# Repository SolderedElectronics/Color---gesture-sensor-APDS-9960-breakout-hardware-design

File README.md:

# Color and gesture sensor APDS-9960 breakout Hardware Design

## About the Product

|  |
| :----------------------------------------------------------: |
| [Buy Color and gesture sensor APDS-9960 breakout](https://www.solde.red/333002) |

The APDS-9960 is a small sensor that measures four things at once. It recognizes the movements you make in front of it (up, down, left, right) and it can identify the proximity of the object, so you have two more movements: to the sensor and from the sensor. In addition, it has an ambient light sensor and a color sensor which gives red, green, and blue (RGB) colors as output. This sensor with many features was even built into the Samsung Galaxy S5 smartphone.

All gestures are detected at a distance of 10 to 20 cm and it has built-in UV and IR filters to make sure it won’t be confused by other sources of light. Connected using well-known I2C communication.

---

## Repository Contents

This repository contains all design files for Color and gesture sensor APDS-9960 breakout, organized as follows:

- **`CAD` folder**: Contains KiCAD design files, including:
  - Schematics
  - PCB layout
  - Panel PCB layout
  - Source 3D files in Fusion360, if any
  - All files are sorted by version with a detailed change log.
- **`OUTPUTS` folder**: Includes all production-ready files, such as:
  - Bill of Materials (BOM) and interactive BOM (iBOM)
  - PDF versions of schematics
  - 3D `.step` file of the board
  - 3D-printable models
  - Gerber files for PCB manufacturing
  - Image of the pinout of the board
  - Product image
  - Compliance, legal and generic sales documents

Refer to the `Change Log` in the CAD folder for details about updates between versions.

---

## Learn More About the Product

Beyond the repository, explore the following resources:

### Soldered Verify

The **Soldered Verify** system ensures every board you purchase from Soldered is fully functional. It also provides access to exclusive test data for your product. To get started, find the unique Soldered Verify ID on your product's packaging and enter the ID on the [Soldered Verify page](https://soldered.com/verify/) to access test results and additional product details.

### Soldered Community

Soldered Community is your go-to place for technical support. Our engineers track and answer all questions posted there, and it’s a great space for the maker community. Get answers to your questions and solutions for your challenges at [Soldered Community](https://soldered.com/community).

### solde.red

solde.red is an ultimate URL shortener and information hub. Access it by typing solde.red/ followed by your product SKU, e.g., [solde.red/333000](https://solde.red/333000), to find getting-started guides, datasheets, open-source hardware and software files, certifications, images, pinouts, and more. Read more about the shortener [here](https://solde.red/info/).

---

## Contributing

Contributions are welcome! Here’s how you can get involved:

- Submit pull requests to enhance the design or fix issues.
- Report bugs or problems by opening an issue.

We encourage community collaboration to make this product even better.

---

## About Soldered

[Soldered for Makers](https://soldered.com) specializes in designing and manufacturing electronic products tailored for enthusiasts, ranging from hobbyists to professionals. Our portfolio includes electronic boards, sensors, and actuators that are widely utilized in fields such as microelectronics, mechatronics, robotics, programming, and IoT. Every product we offer is designed in-house and built upon open-source hardware and software platforms. Proudly certified and manufactured within the European Union, our catalog likely includes the product you need for your project.

We complement these products with comprehensive tutorials and manuals, product descriptions, schematics, programming codes, and project examples. Our round-the-clock [customer and technical support](https://soldered.com/community) is available for all our products, irrespective of the sales channel. Soldered’s success and services reflect our maker community’s unwavering [trust](https://www.trustpilot.com/review/soldered.com), for which we are deeply grateful. Join our community and create using Soldered products.

---

## License

All Soldered open-source hardware (OSH) is under The TAPR Open Hardware License. Read more in the LICENSE file located in this repository.

**Disclaimer:**

No warranty - all designs in this repository are distributed in the hope that they will be useful, but without any warranty. They are provided "AS IS", therefore without warranty of any kind, either expressed or implied. The entire quality and performance of what you do with the contents of this repository are your responsibility. In no event Soldered Electronics will be liable for your damages, or losses, including any general, special, incidental, or consequential damage arising out of the use or inability to use the contents of this repository. 

---

## Have fun!

Thank you for your support from your fellow makers at Soldered Electronics.

Happy Making!

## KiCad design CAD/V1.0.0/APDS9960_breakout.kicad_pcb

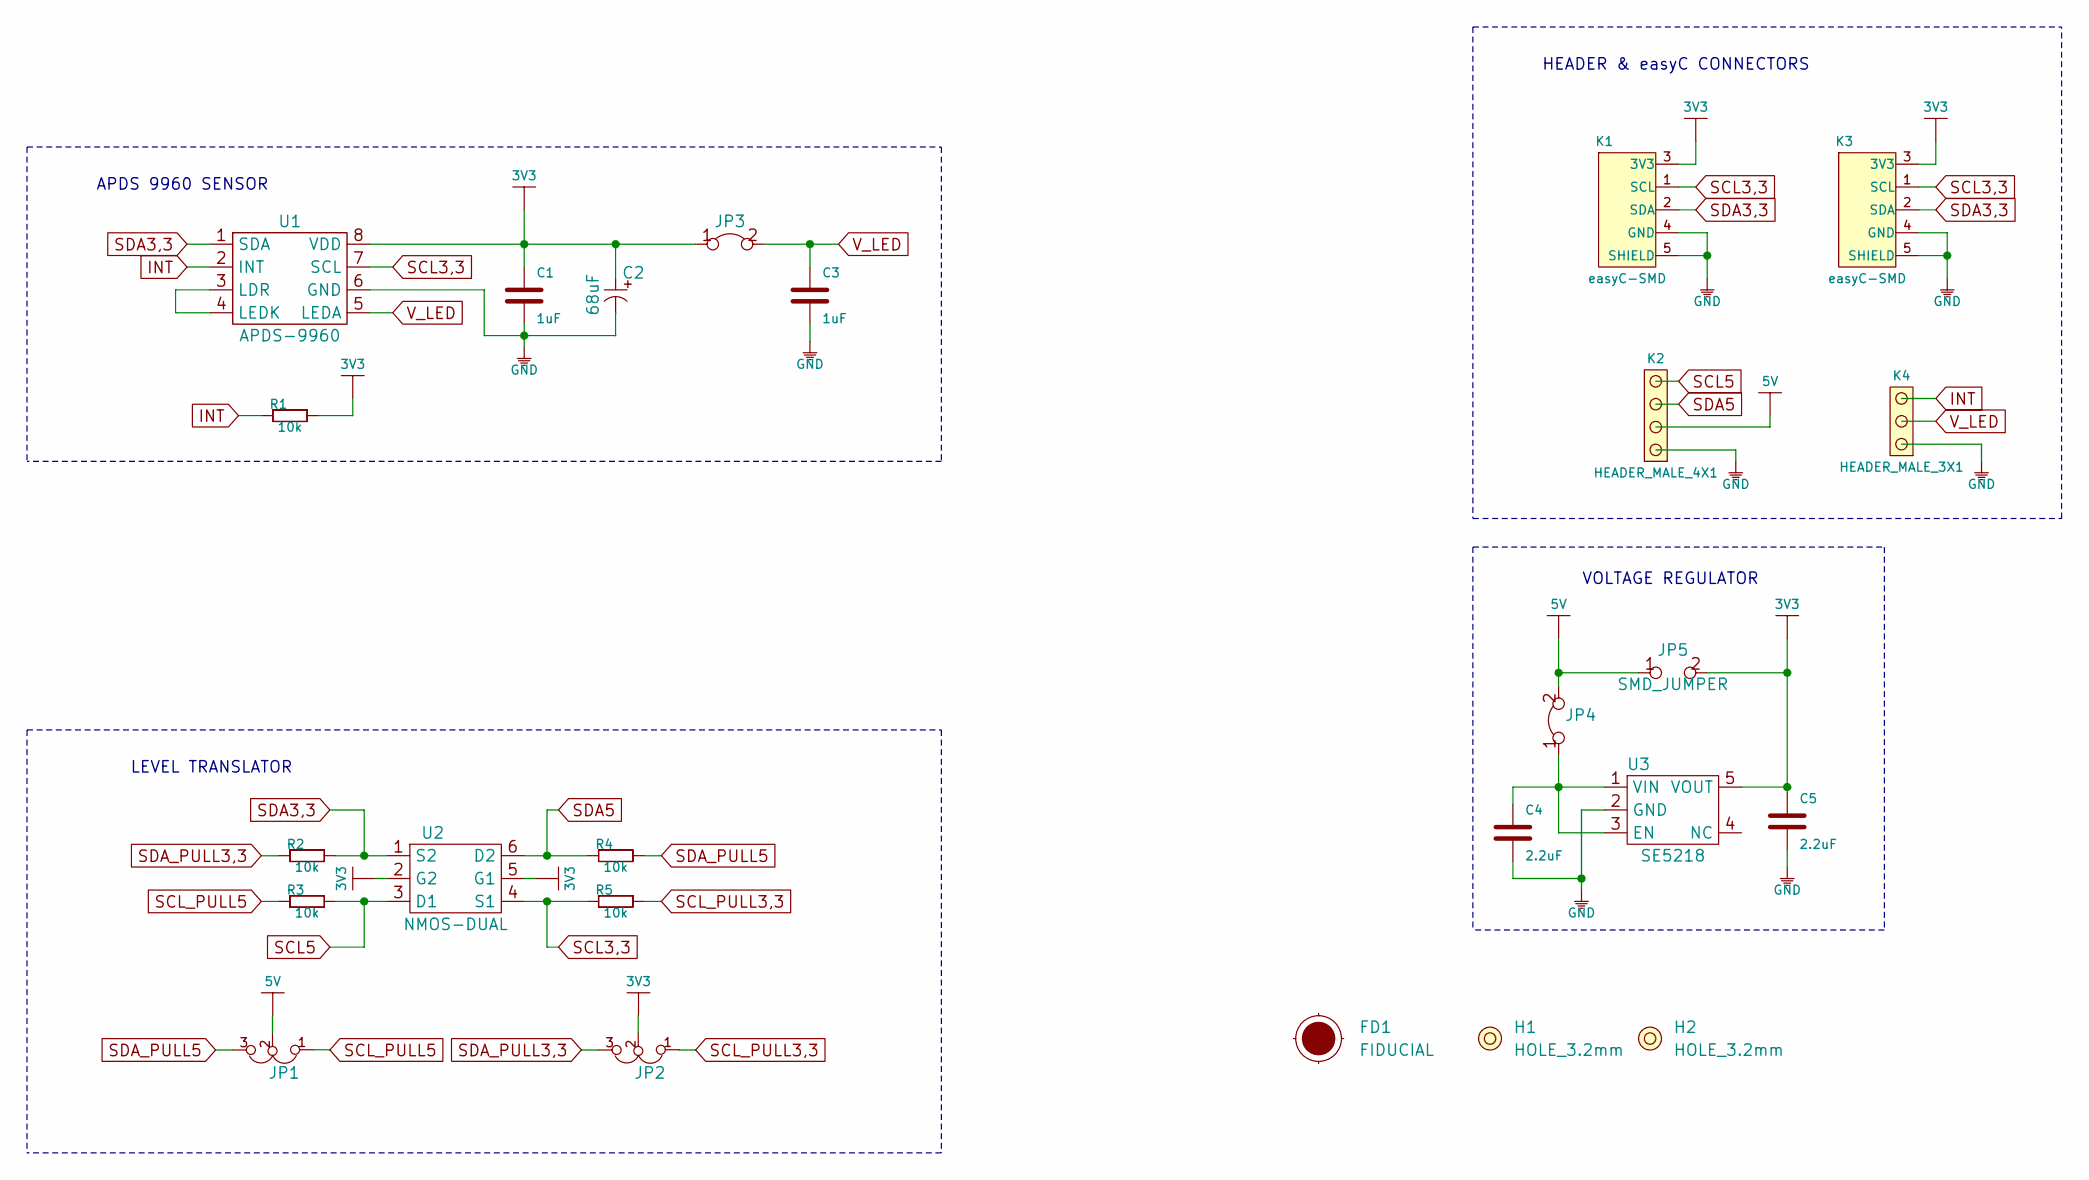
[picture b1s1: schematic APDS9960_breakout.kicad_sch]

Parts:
C1, C3: 1uF; 0603C
C2: 68uF; 1210C_tantal
C4, C5: 2.2uF; 0603C
FD1: FIDUCIAL; FIDUCIAL_23
H1, H2: HOLE_3.2mm
JP1, JP2: SMD_JUMPER_3_PAD_TRACE
JP3, JP4: SMD-JUMPER-CONNECTED_TRACE_SLODERMASK
JP5: SMD_JUMPER
K1, K3: easyC-SMD; easyC-connector
K2: HEADER_MALE_4X1
K4: HEADER_MALE_3X1
R1, R2, R3, R4, R5: 10k; 0603R
U1: APDS-9960
U2: NMOS-DUAL; SOT-363
U3: SE5218; SOT-23-5

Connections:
3V3: C1.2, C2.1 (+), C5.2, JP2.2, JP3.1, JP5.2, K1.3 (3V3), K3.3 (3V3), R1.2, U1.8 (VDD), U2.2 (G2), U2.5 (G1), U3.5 (VOUT)
5V: JP1.2, JP4.2, JP5.1, K2.2
GND: C1.1, C2.2 (-), C3.1, C4.1, C5.1, K1.4 (GND), K1.5 (SHIELD), K2.1, K3.4 (GND), K3.5 (SHIELD), K4.1, U1.6 (GND), U3.2 (GND)
INT: K4.3, R1.1, U1.2 (INT)
unnamed: C4.2, JP4.1, U3.1 (VIN), U3.3 (EN)
unnamed: U1.3 (LDR), U1.4 (LEDK)
SCL3,3: K1.1 (SCL), K3.1 (SCL), R5.1, U1.7 (SCL), U2.4 (S1)
SCL5: K2.4, R3.2, U2.3 (D1)
SCL_PULL3,3: JP2.1, R5.2
SCL_PULL5: JP1.1, R3.1
SDA3,3: K1.2 (SDA), K3.2 (SDA), R2.2, U1.1 (SDA), U2.1 (S2)
SDA5: K2.3, R4.1, U2.6 (D2)
SDA_PULL3,3: JP2.3, R2.1
SDA_PULL5: JP1.3, R4.2
V_LED: C3.2, JP3.2, K4.2, U1.5 (LEDA)

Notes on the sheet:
APDS 9960 SENSOR
LEVEL TRANSLATOR
HEADER & easyC CONNECTORS
VOLTAGE REGULATOR

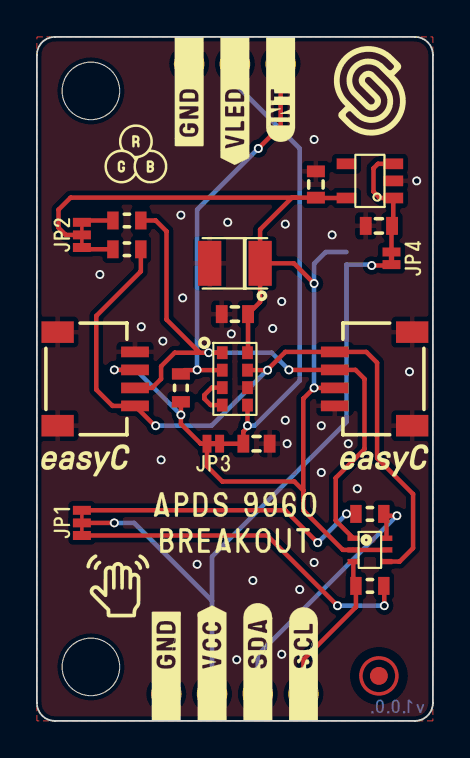
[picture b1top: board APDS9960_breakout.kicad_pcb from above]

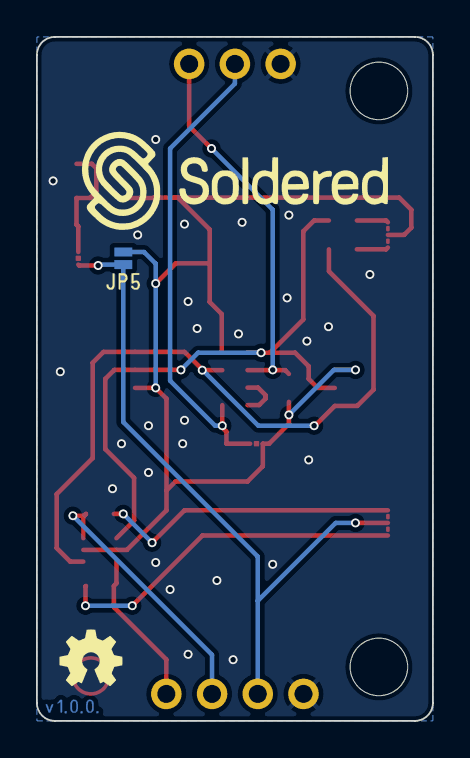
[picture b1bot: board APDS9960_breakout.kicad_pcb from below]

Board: 2 copper layers, 22.0 x 38.0 mm, 26 parts (2 on the bottom side), 15 nets.

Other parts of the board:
Ref**: Val**; Version1.0.0.

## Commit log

2022-08-06 Updating open source files.
